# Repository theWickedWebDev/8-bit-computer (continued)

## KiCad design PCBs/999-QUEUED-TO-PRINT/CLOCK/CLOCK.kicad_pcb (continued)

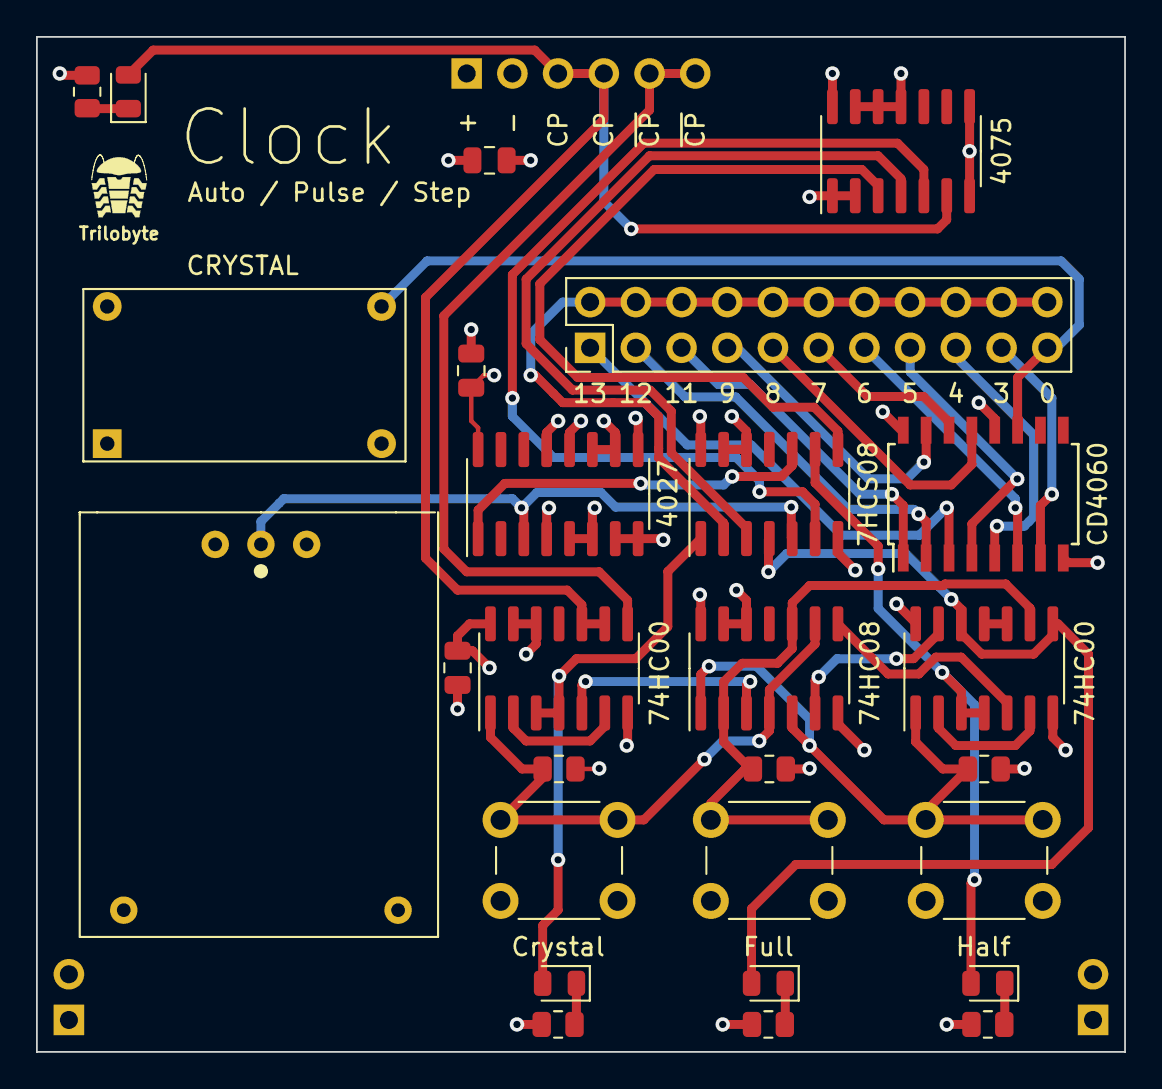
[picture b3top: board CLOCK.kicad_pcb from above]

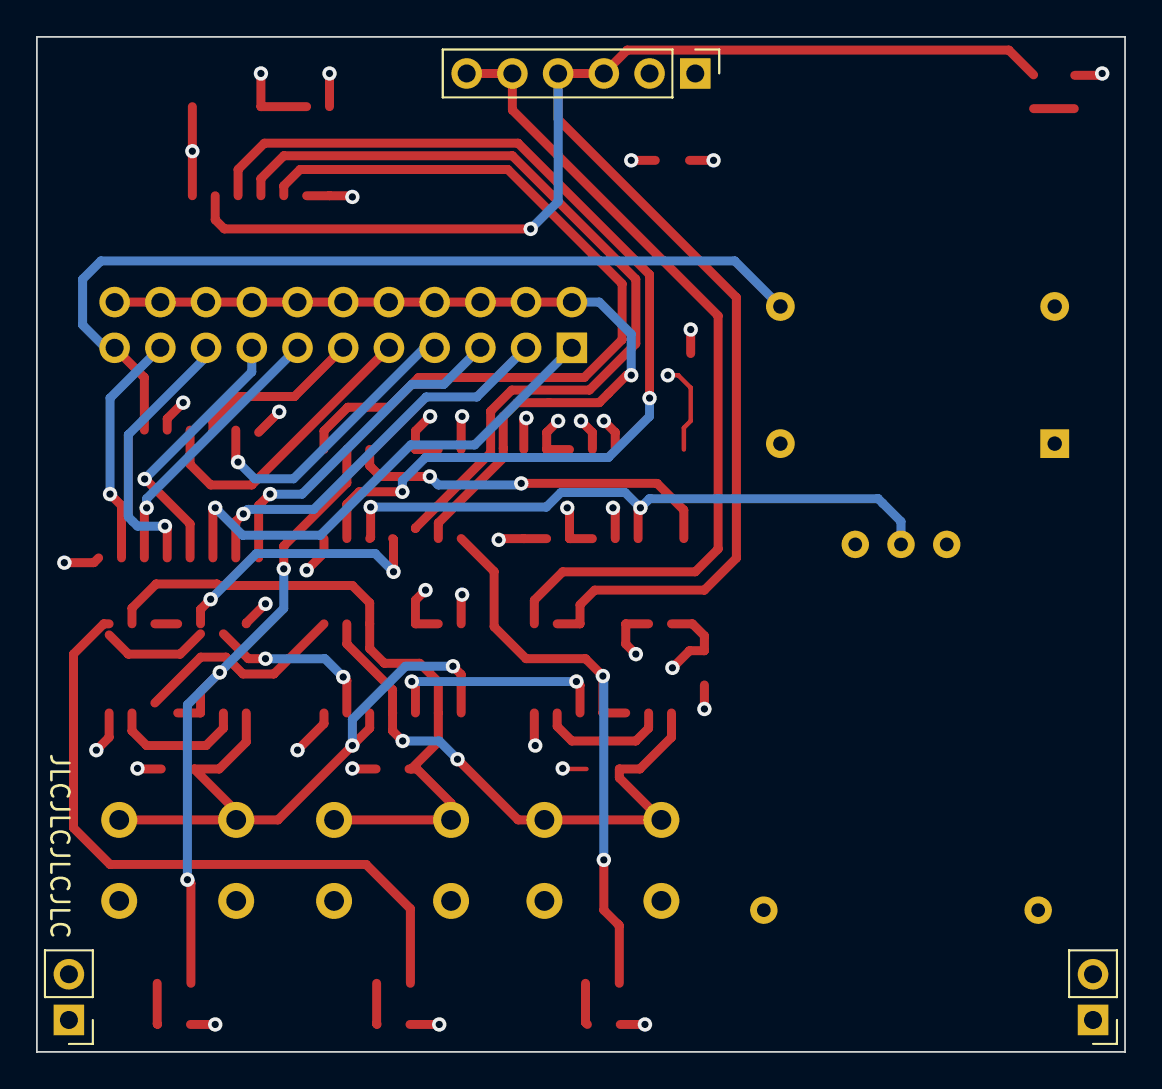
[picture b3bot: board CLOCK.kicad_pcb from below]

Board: 4 copper layers, 60.5 x 56.4 mm, 30 parts (3 on the bottom side), 37 nets.

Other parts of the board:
U4#2: DebouncedButton; COMP-DebounceButton-Component

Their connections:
/MANUAL_FULL_CLOCK: U4#2.3 (Q); also elsewhere on the board
GND: U4#2.2 (Gnd); also elsewhere on the board
VCC: U4#2.1 (Vcc); also elsewhere on the board

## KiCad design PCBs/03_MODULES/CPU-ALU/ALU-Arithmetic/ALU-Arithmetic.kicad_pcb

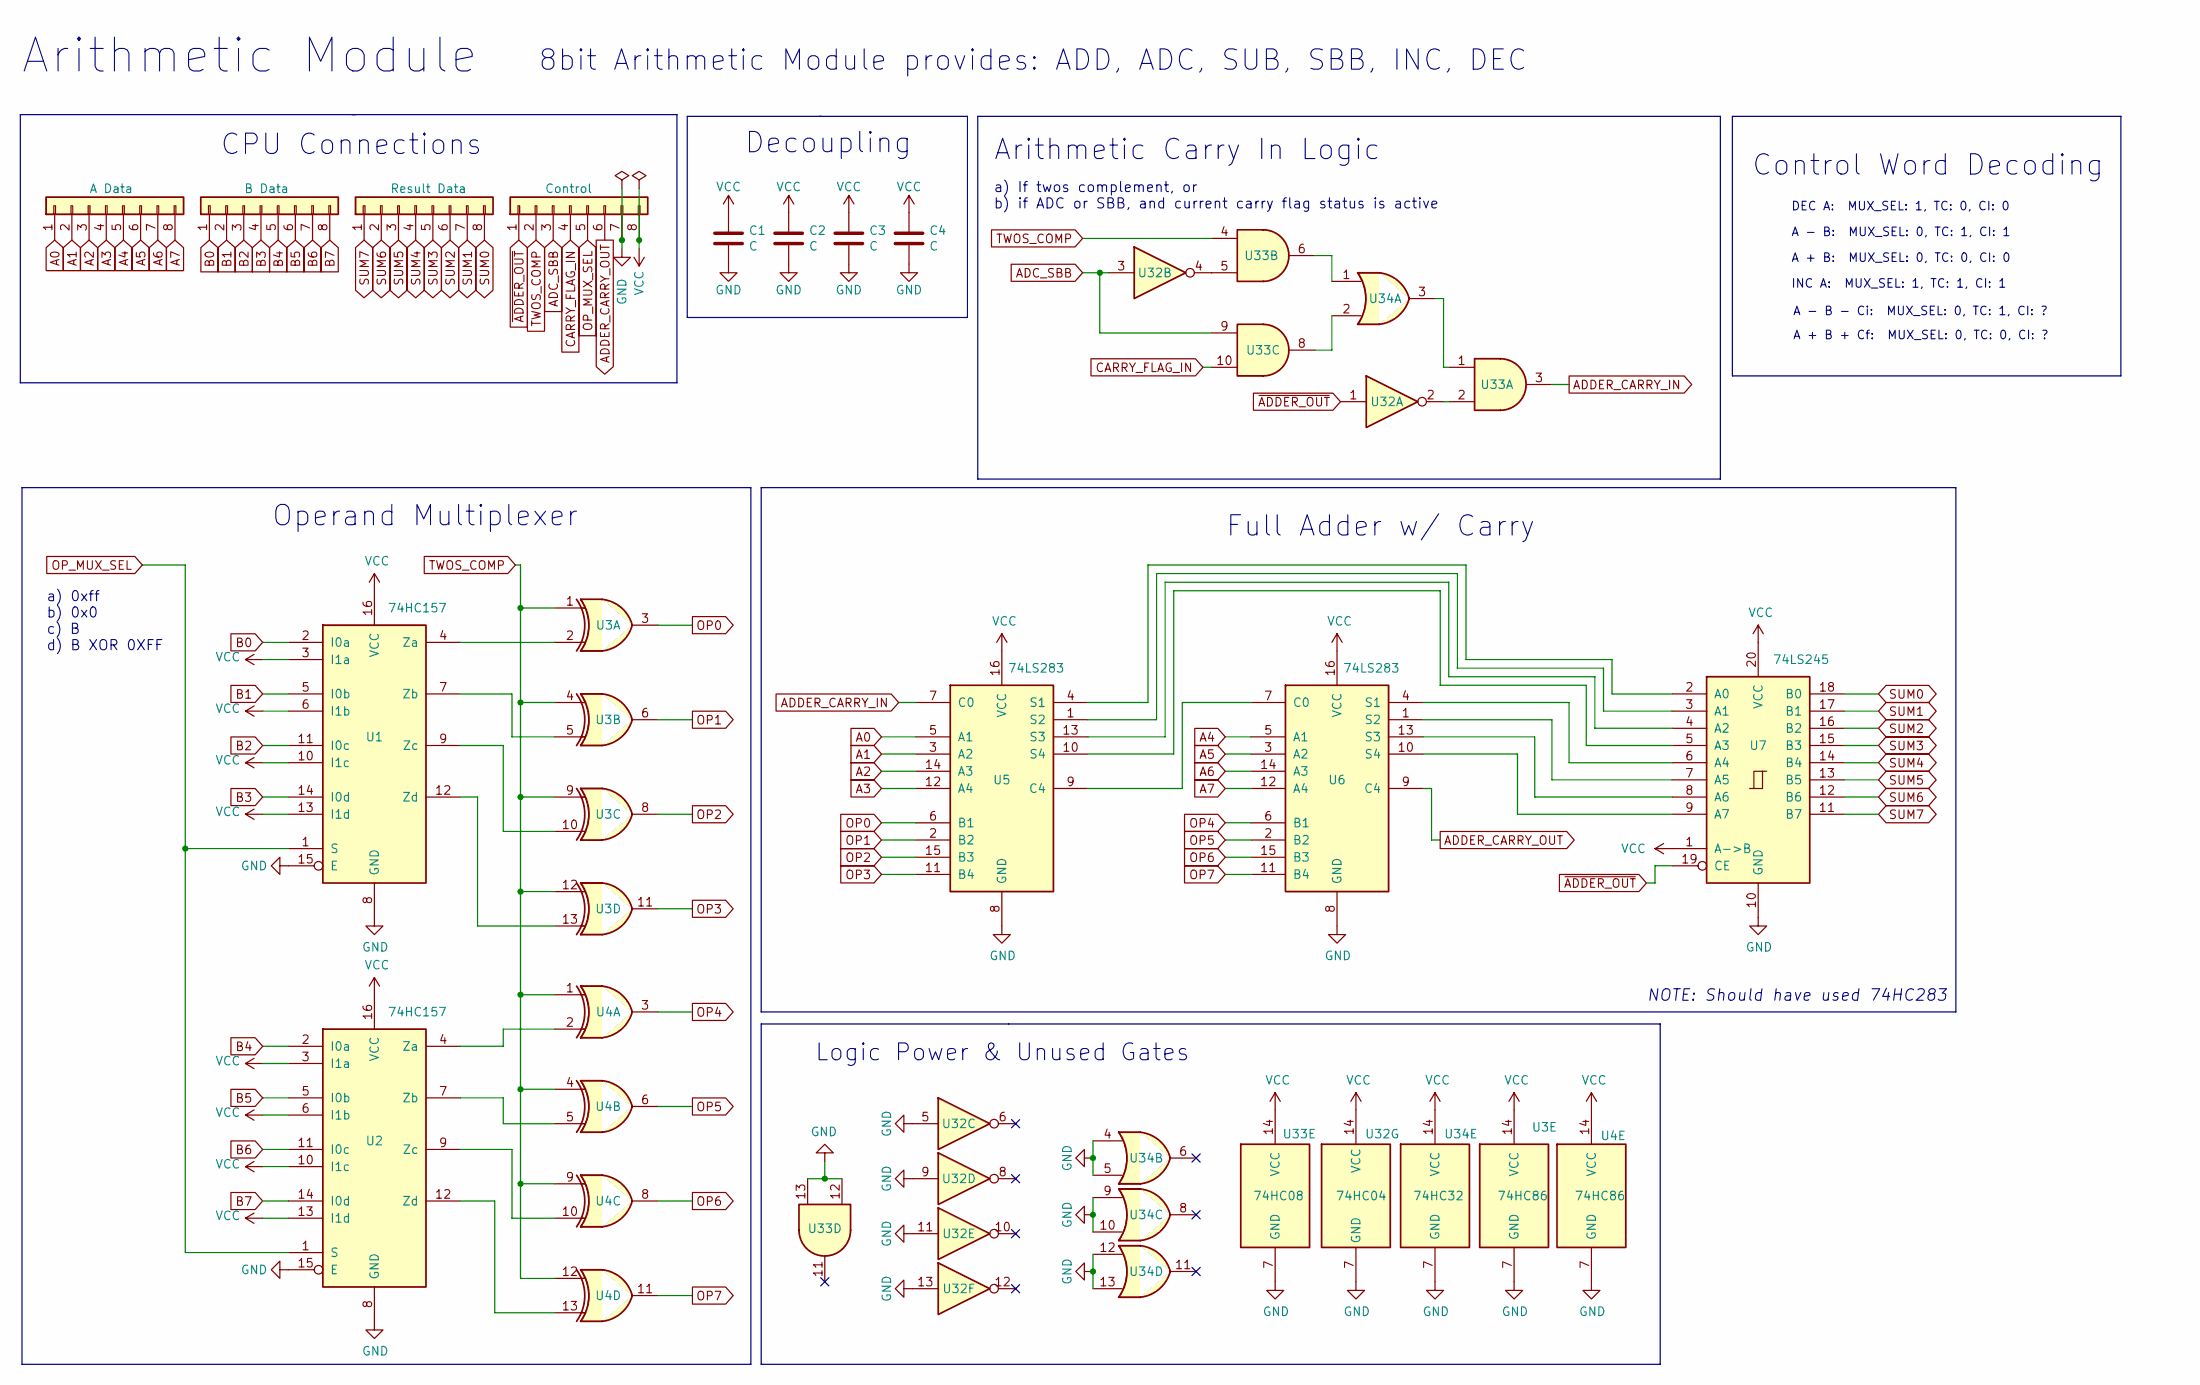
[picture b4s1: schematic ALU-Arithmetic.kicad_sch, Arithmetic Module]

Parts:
C1, C2, C3, C4: C; C_0805_2012Metric
J1, J2, J3, J4: Conn_01x08; PinHeader_1x08_P2.54mm_Vertical
U1, U2: 74HC157; TSSOP-16_4.4x5mm_P0.65mm
U3, U4: 74HC86; TSSOP-14_4.4x5mm_P0.65mm
U5, U6: 74LS283; SOIC-16W_5.3x10.2mm_P1.27mm
U7: 74LS245; TSSOP-20_4.4x6.5mm_P0.65mm
U32: 74HC04; TSSOP-14_4.4x5mm_P0.65mm
U33: 74HC08; TSSOP-14_4.4x5mm_P0.65mm
U34: 74HC32; TSSOP-14_4.4x5mm_P0.65mm

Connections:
A0: J1.1, U5.5 (A1)
A1: J1.2, U5.3 (A2)
A2: J1.3, U5.14 (A3)
A3: J1.4, U5.12 (A4)
A4: J1.5, U6.5 (A1)
A5: J1.6, U6.3 (A2)
A6: J1.7, U6.14 (A3)
A7: J1.8, U6.12 (A4)
ADC_SBB: J4.3, U32.3, U33.9
ADDER_CARRY_IN: U5.7 (C0), U33.3
ADDER_CARRY_OUT: J4.6, U6.9 (C4)
B0: J2.1, U1.2 (I0a)
B1: J2.2, U1.5 (I0b)
B2: J2.3, U1.11 (I0c)
B3: J2.4, U1.14 (I0d)
B4: J2.5, U2.2 (I0a)
B5: J2.6, U2.5 (I0b)
B6: J2.7, U2.11 (I0c)
B7: J2.8, U2.14 (I0d)
CARRY_FLAG_IN: J4.4, U33.10
unnamed: U1.4 (Za), U3.2
unnamed: U1.7 (Zb), U3.5
unnamed: U1.9 (Zc), U3.10
unnamed: U1.12 (Zd), U3.13
unnamed: U2.4 (Za), U4.2
unnamed: U2.7 (Zb), U4.5
unnamed: U2.9 (Zc), U4.10
unnamed: U2.12 (Zd), U4.13
unnamed: U5.1 (S2), U7.3 (A1)
unnamed: U5.4 (S1), U7.2 (A0)
unnamed: U5.9 (C4), U6.7 (C0)
unnamed: U5.10 (S4), U7.5 (A3)
unnamed: U5.13 (S3), U7.4 (A2)
unnamed: U6.1 (S2), U7.7 (A5)
unnamed: U6.4 (S1), U7.6 (A4)
unnamed: U6.10 (S4), U7.9 (A7)
unnamed: U6.13 (S3), U7.8 (A6)
unnamed: U32.2, U33.2
unnamed: U32.4, U33.5
unnamed: U33.1, U34.3
unnamed: U33.6, U34.1
unnamed: U33.8, U34.2
OP0: U3.3, U5.6 (B1)
OP1: U3.6, U5.2 (B2)
OP2: U3.8, U5.15 (B3)
OP3: U3.11, U5.11 (B4)
OP4: U4.3, U6.6 (B1)
OP5: U4.6, U6.2 (B2)
OP6: U4.8, U6.15 (B3)
OP7: U4.11, U6.11 (B4)
OP_MUX_SEL: J4.5, U1.1 (S), U2.1 (S)
SUM0: J3.8, U7.18 (B0)
SUM1: J3.7, U7.17 (B1)
SUM2: J3.6, U7.16 (B2)
SUM3: J3.5, U7.15 (B3)
SUM4: J3.4, U7.14 (B4)
SUM5: J3.3, U7.13 (B5)
SUM6: J3.2, U7.12 (B6)
SUM7: J3.1, U7.11 (B7)
TWOS_COMP: J4.2, U3.1, U3.4, U3.9, U3.12, U4.1, U4.4, U4.9, U4.12, U33.4
VCC: C1.1, C2.1, C3.1, C4.1, J4.8, U1.3 (I1a), U1.6 (I1b), U1.10 (I1c), U1.13 (I1d), U1.16 (VCC), U2.3 (I1a), U2.6 (I1b), U2.10 (I1c), U2.13 (I1d), U2.16 (VCC), U3.14 (VCC), U4.14 (VCC), U5.16 (VCC), U6.16 (VCC), U7.1 (A->B), U7.20 (VCC), U32.14 (VCC), U33.14 (VCC), U34.14 (VCC)
~ADDER_OUT: J4.1, U7.19 (CE), U32.1

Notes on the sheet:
a) 0xff b) 0x0 c) B d) B XOR 0XFF
CPU Connections
NOTE: Should have used 74HC283
8bit Arithmetic Module provides: ADD, ADC, SUB, SBB, INC, DEC
A - B - Ci: MUX_SEL: 0, TC: 1, CI: ?
Logic Power & Unused Gates
A + B + Cf: MUX_SEL: 0, TC: 0, CI: ?
Full Adder w/ Carry
Operand Multiplexer
Arithmetic Module
DEC A: MUX_SEL: 1, TC: 0, CI: 0
a) If twos complement, or b) if ADC or SBB, and current carry flag status is active
Arithmetic Carry In Logic
Decoupling
A - B: MUX_SEL: 0, TC: 1, CI: 1
Control Word Decoding
INC A: MUX_SEL: 1, TC: 1, CI: 1
A + B: MUX_SEL: 0, TC: 0, CI: 0

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
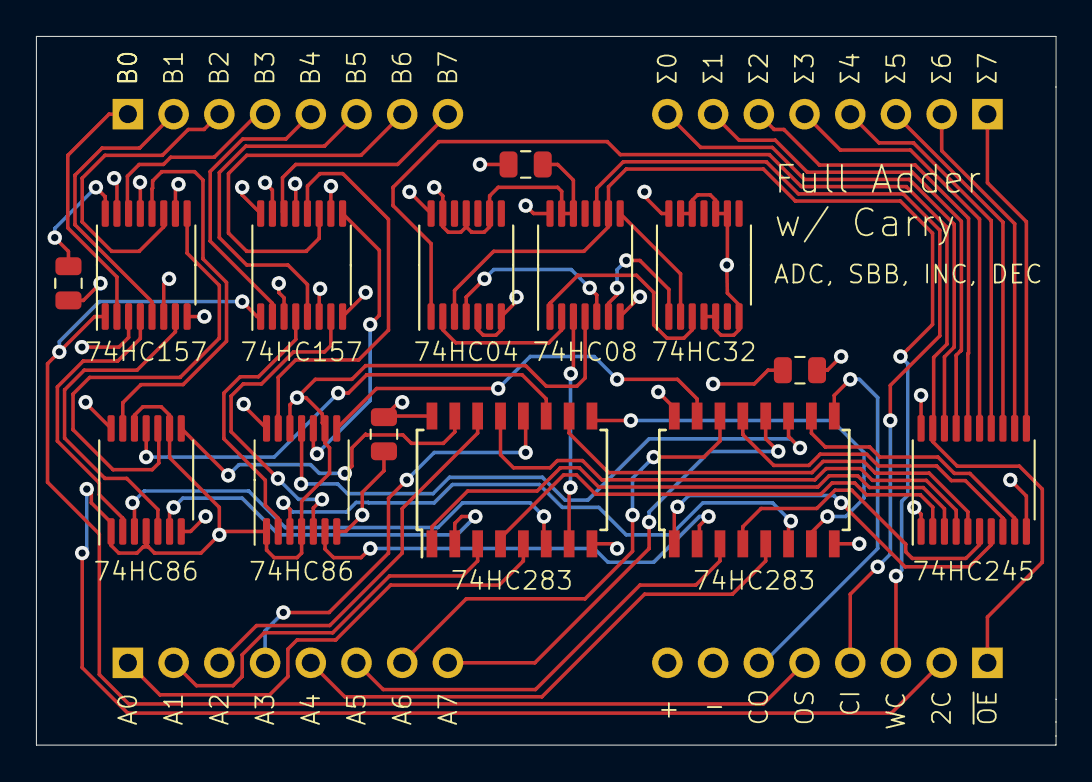
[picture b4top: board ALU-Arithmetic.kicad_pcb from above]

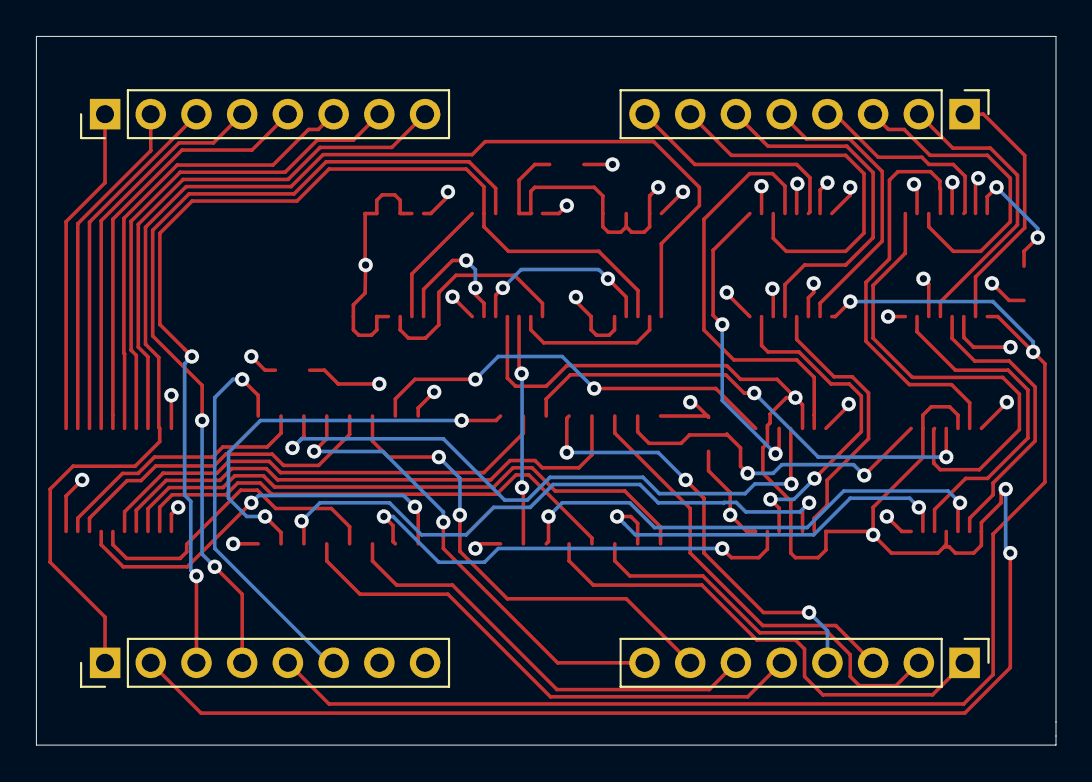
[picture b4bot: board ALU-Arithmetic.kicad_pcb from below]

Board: 4 copper layers, 56.6 x 39.4 mm, 18 parts (4 on the bottom side), 63 nets.

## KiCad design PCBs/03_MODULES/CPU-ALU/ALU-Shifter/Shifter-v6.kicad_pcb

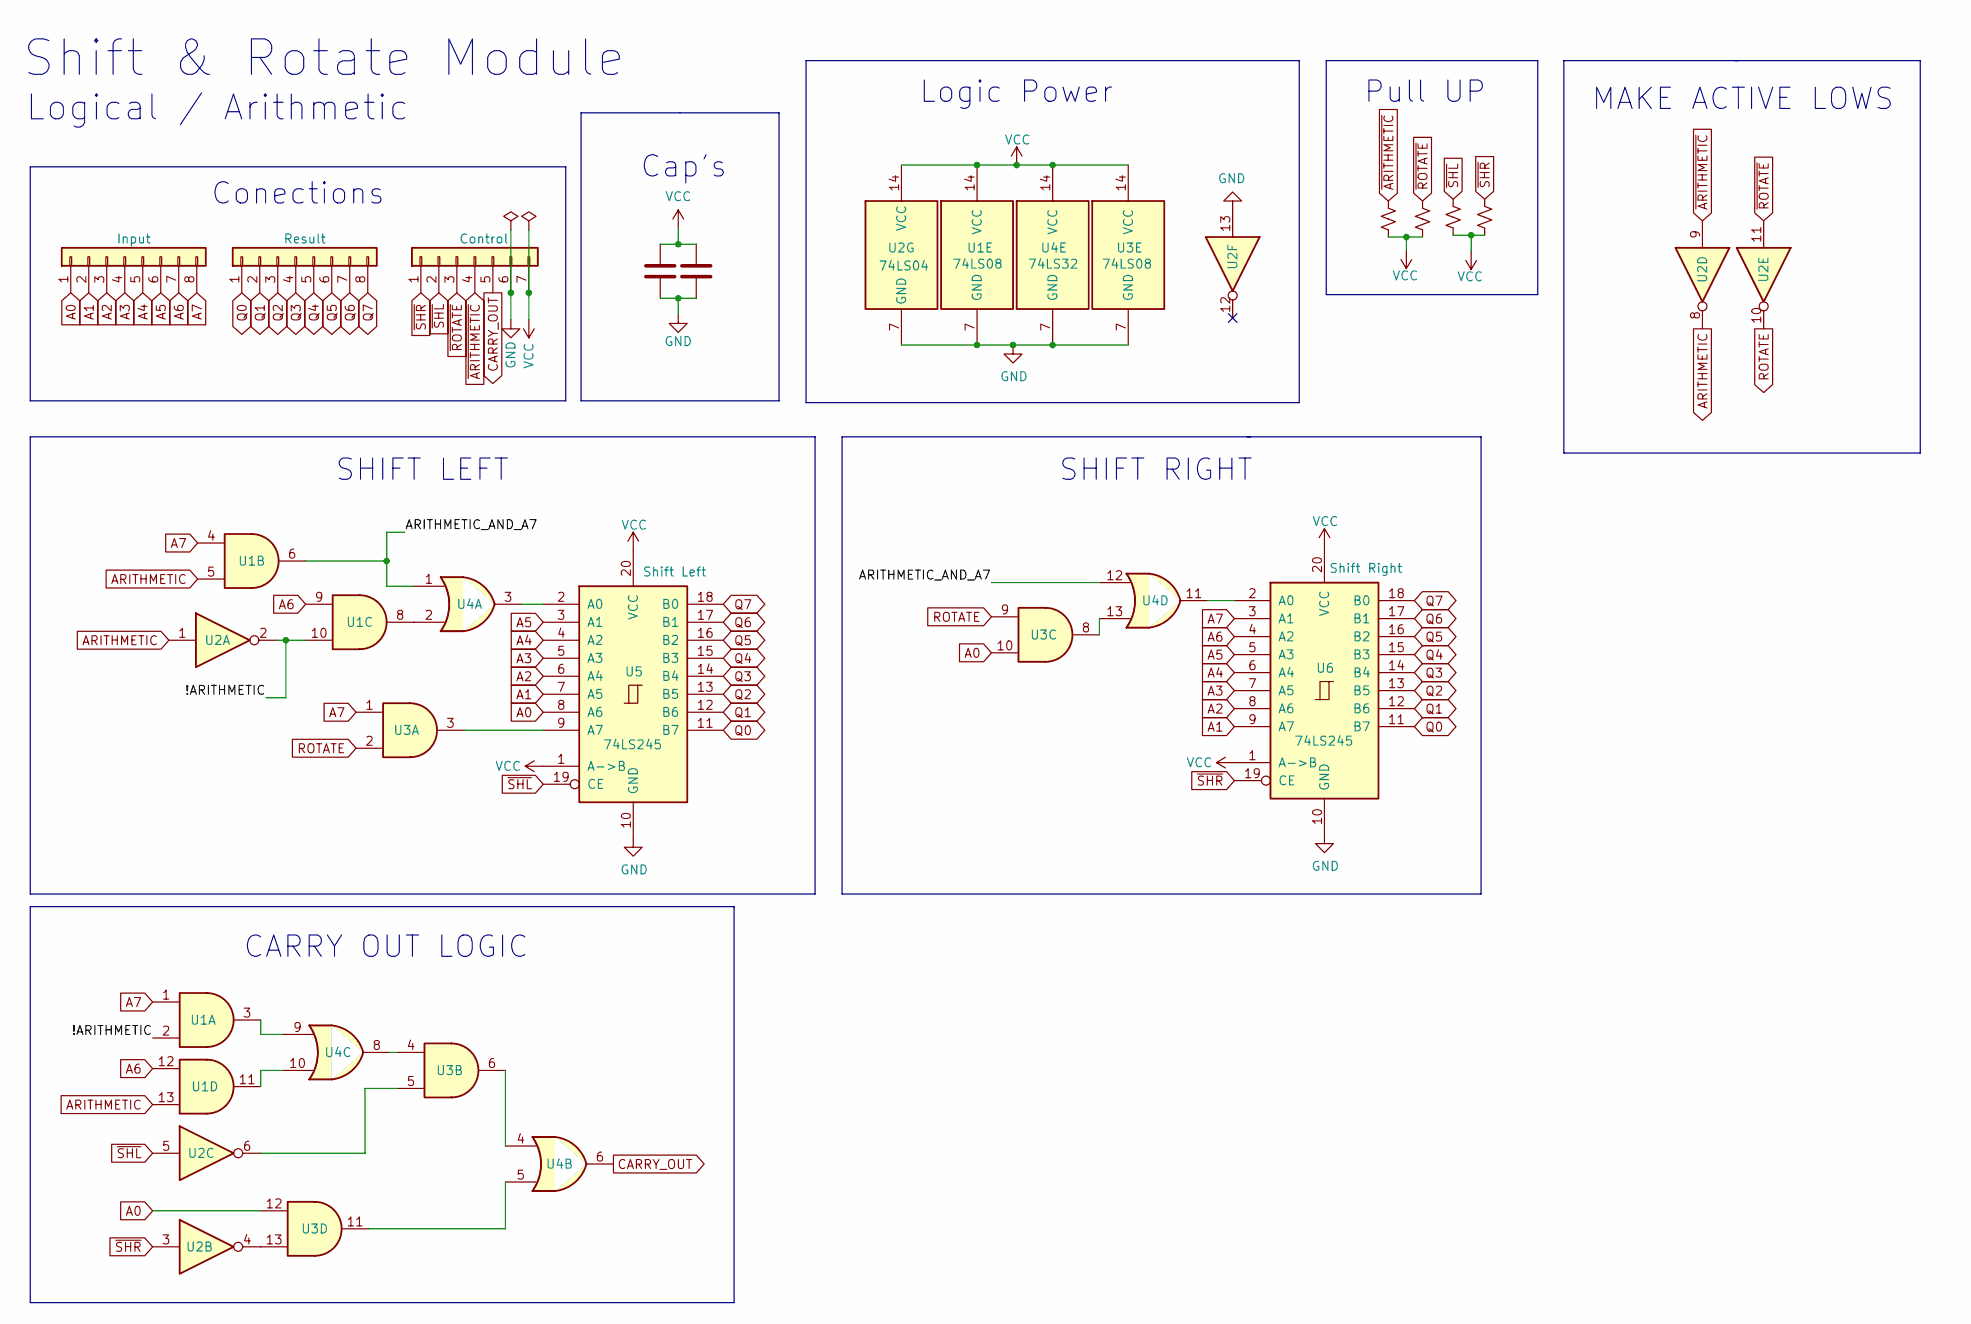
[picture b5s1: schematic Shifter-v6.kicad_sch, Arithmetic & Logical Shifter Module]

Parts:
C1, C2: C; C_0805_2012Metric
J1, J2: Conn_01x08; PinHeader_1x08_P2.54mm_Vertical
J3: Conn_01x07; PinHeader_1x07_P2.54mm_Vertical
R10, R11, R12, R13: R_Small_US; R_0805_2012Metric
U1, U3: 74LS08; TSSOP-14_4.4x5mm_P0.65mm
U2: 74LS04; TSSOP-14_4.4x5mm_P0.65mm
U4: 74LS32; TSSOP-14_4.4x5mm_P0.65mm
U5, U6: 74LS245; TSSOP-20_4.4x6.5mm_P0.65mm

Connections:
/!ARITHMETIC: U1.2, U1.10, U2.2
/ARITHMETIC_AND_A7: U1.6, U4.1, U4.12
A0: J1.1, U3.10, U3.12, U5.8 (A6)
A1: J1.2, U5.7 (A5), U6.9 (A7)
A2: J1.3, U5.6 (A4), U6.8 (A6)
A3: J1.4, U5.5 (A3), U6.7 (A5)
A4: J1.5, U5.4 (A2), U6.6 (A4)
A5: J1.6, U5.3 (A1), U6.5 (A3)
A6: J1.7, U1.9, U1.12, U6.4 (A2)
A7: J1.8, U1.1, U1.4, U3.1, U6.3 (A1)
ARITHMETIC: U1.5, U1.13, U2.1, U2.8
CARRY_OUT: J3.5, U4.6
GND: C1.1, C2.1, J3.6, U1.7 (GND), U2.7 (GND), U2.13, U3.7 (GND), U4.7 (GND), U5.10 (GND), U6.10 (GND)
unnamed: U1.3, U4.9
unnamed: U1.8, U4.2
unnamed: U1.11, U4.10
unnamed: U2.4, U3.13
unnamed: U2.6, U3.5
unnamed: U3.3, U5.9 (A7)
unnamed: U3.4, U4.8
unnamed: U3.6, U4.4
unnamed: U3.8, U4.13
unnamed: U3.11, U4.5
unnamed: U4.3, U5.2 (A0)
unnamed: U4.11, U6.2 (A0)
Q0: J2.1, U5.11 (B7), U6.11 (B7)
Q1: J2.2, U5.12 (B6), U6.12 (B6)
Q2: J2.3, U5.13 (B5), U6.13 (B5)
Q3: J2.4, U5.14 (B4), U6.14 (B4)
Q4: J2.5, U5.15 (B3), U6.15 (B3)
Q5: J2.6, U5.16 (B2), U6.16 (B2)
Q6: J2.7, U5.17 (B1), U6.17 (B1)
Q7: J2.8, U5.18 (B0), U6.18 (B0)
ROTATE: U2.10, U3.2, U3.9
~ARITHMETIC: J3.4, R13.1, U2.9
~ROTATE: J3.3, R10.1, U2.11
~SHL: J3.2, R11.1, U2.5, U5.19 (CE)
~SHR: J3.1, R12.1, U2.3, U6.19 (CE)

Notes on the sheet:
Cap's
Shift & Rotate Module
SHIFT RIGHT
SHIFT LEFT
Conections
Logic Power
MAKE ACTIVE LOWS
Pull UP
Logical / Arithmetic
CARRY OUT LOGIC

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
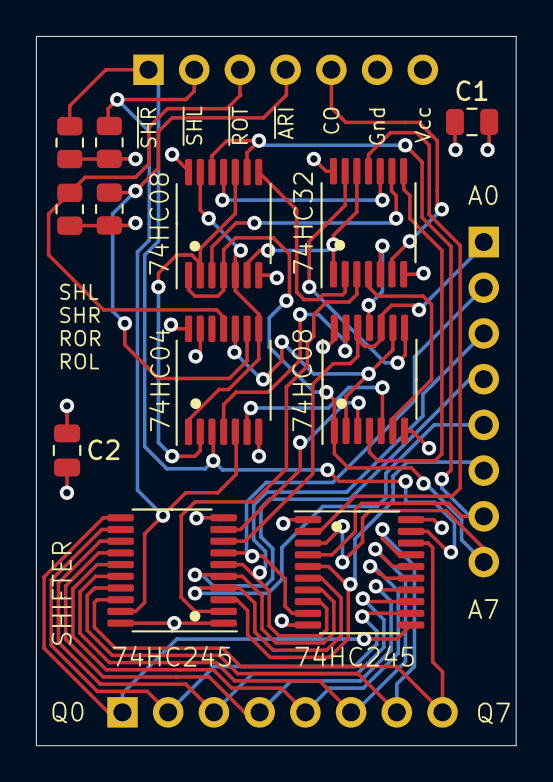
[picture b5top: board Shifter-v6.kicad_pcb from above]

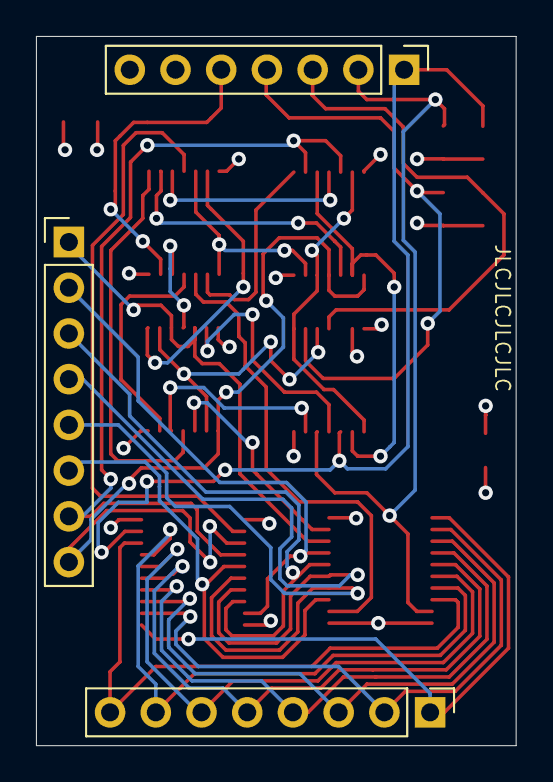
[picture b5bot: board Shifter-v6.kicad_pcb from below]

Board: 4 copper layers, 26.7 x 39.4 mm, 15 parts (3 on the bottom side), 39 nets.

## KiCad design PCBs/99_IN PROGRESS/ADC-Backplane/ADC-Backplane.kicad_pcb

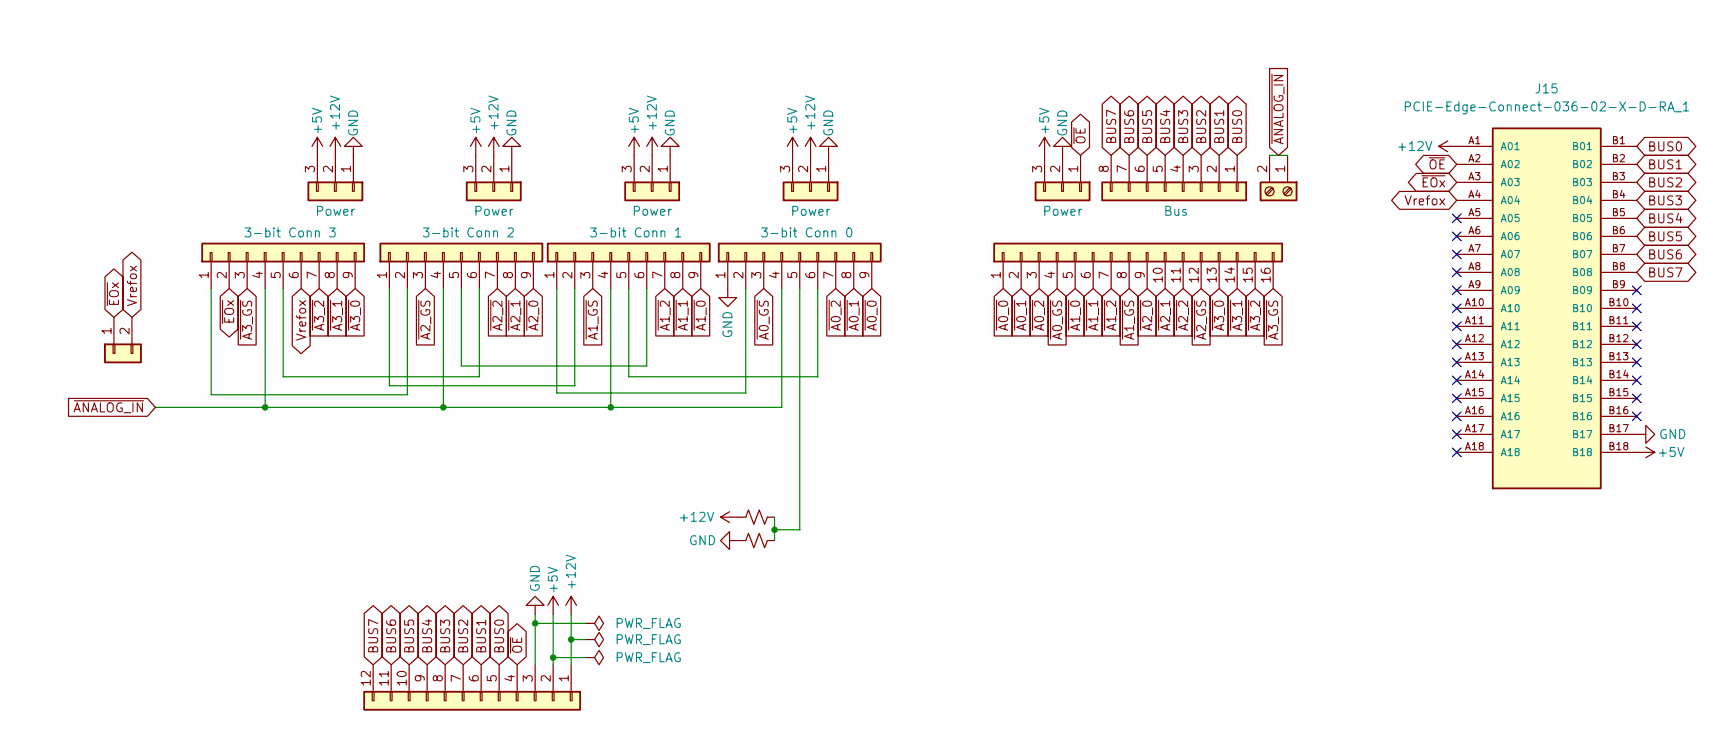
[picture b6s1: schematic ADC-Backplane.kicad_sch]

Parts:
J1: Conn_01x02; PinHeader_1x02_P2.54mm_Horizontal
J2, J4, J7, J9: Conn_01x09; PinSocket_1x09_P2.54mm_Vertical
J3, J6, J8, J10, J11: Conn_01x03; PinSocket_1x03_P2.54mm_Vertical
J5: Conn_01x12; PinHeader_1x12_P2.54mm_Horizontal
J12: Conn_01x16; PinSocket_1x16_P2.54mm_Vertical
J13: Conn_01x08; PinSocket_1x08_P2.54mm_Vertical
J14: Screw_Terminal_01x02; TerminalBlock_TE_282834-2_1x02_P2.54mm_Horizontal
J15: PCIE-Edge-Connect-036-02-X-D-RA_1; BUS_PCIexpress_x1; PARTREV D
R1, R2: R_Small_US; R_0805_2012Metric

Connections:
+5V: J3.3, J5.2, J6.3, J8.3, J10.3, J11.3, J15.B18
+12V: J3.2, J5.1, J6.2, J8.2, J10.2, J15.A1 (A01), R1.2
BUS0: J5.5, J13.1, J15.B1 (B01)
BUS1: J5.6, J13.2, J15.B2 (B02)
BUS2: J5.7, J13.3, J15.B3 (B03)
BUS3: J5.8, J13.4, J15.B4 (B04)
BUS4: J5.9, J13.5, J15.B5 (B05)
BUS5: J5.10, J13.6, J15.B6 (B06)
BUS6: J5.11, J13.7, J15.B7 (B07)
BUS7: J5.12, J13.8, J15.B8 (B08)
GND: J3.1, J5.3, J6.1, J8.1, J9.1, J10.1, J11.2, J15.B17, R2.2
unnamed: J2.1, J4.2
unnamed: J2.5, J4.6
unnamed: J4.1, J7.2
unnamed: J4.5, J7.6
unnamed: J7.1, J9.2
unnamed: J7.5, J9.6
unnamed: J9.5, R1.1, R2.1
Vrefox: J1.2, J2.6, J15.A4 (A04)
~A0_0: J9.9, J12.1
~A0_1: J9.8, J12.2
~A0_2: J9.7, J12.3
~A0_GS: J9.3, J12.4
~A1_0: J7.9, J12.5
~A1_1: J7.8, J12.6
~A1_2: J7.7, J12.7
~A1_GS: J7.3, J12.8
~A2_0: J4.9, J12.9
~A2_1: J4.8, J12.10
~A2_2: J4.7, J12.11
~A2_GS: J4.3, J12.12
~A3_0: J2.9, J12.13
~A3_1: J2.8, J12.14
~A3_2: J2.7, J12.15
~A3_GS: J2.3, J12.16
~ANALOG_IN: J2.4, J4.4, J7.4, J9.4, J14.1, J14.2
~EOx: J1.1, J2.2, J15.A3 (A03)
~OE: J5.4, J11.1, J15.A2 (A02)

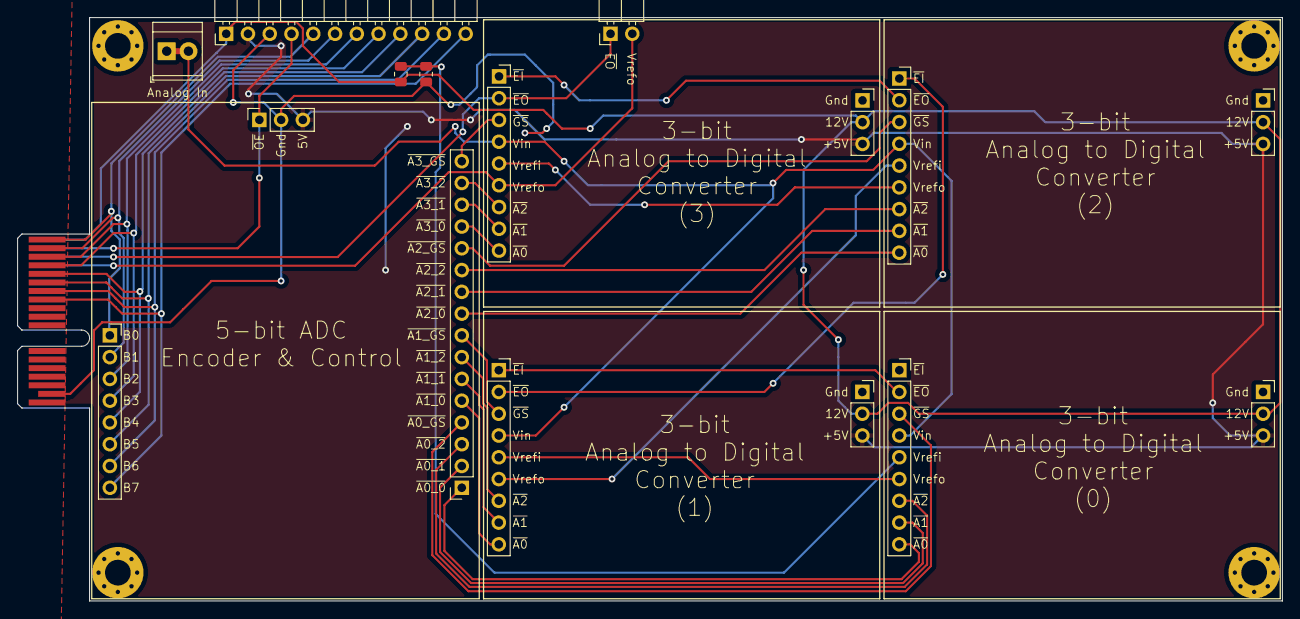
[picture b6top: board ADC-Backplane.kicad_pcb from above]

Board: 2 copper layers, 147.6 x 68.1 mm, 17 parts (0 on the bottom side), 38 nets.

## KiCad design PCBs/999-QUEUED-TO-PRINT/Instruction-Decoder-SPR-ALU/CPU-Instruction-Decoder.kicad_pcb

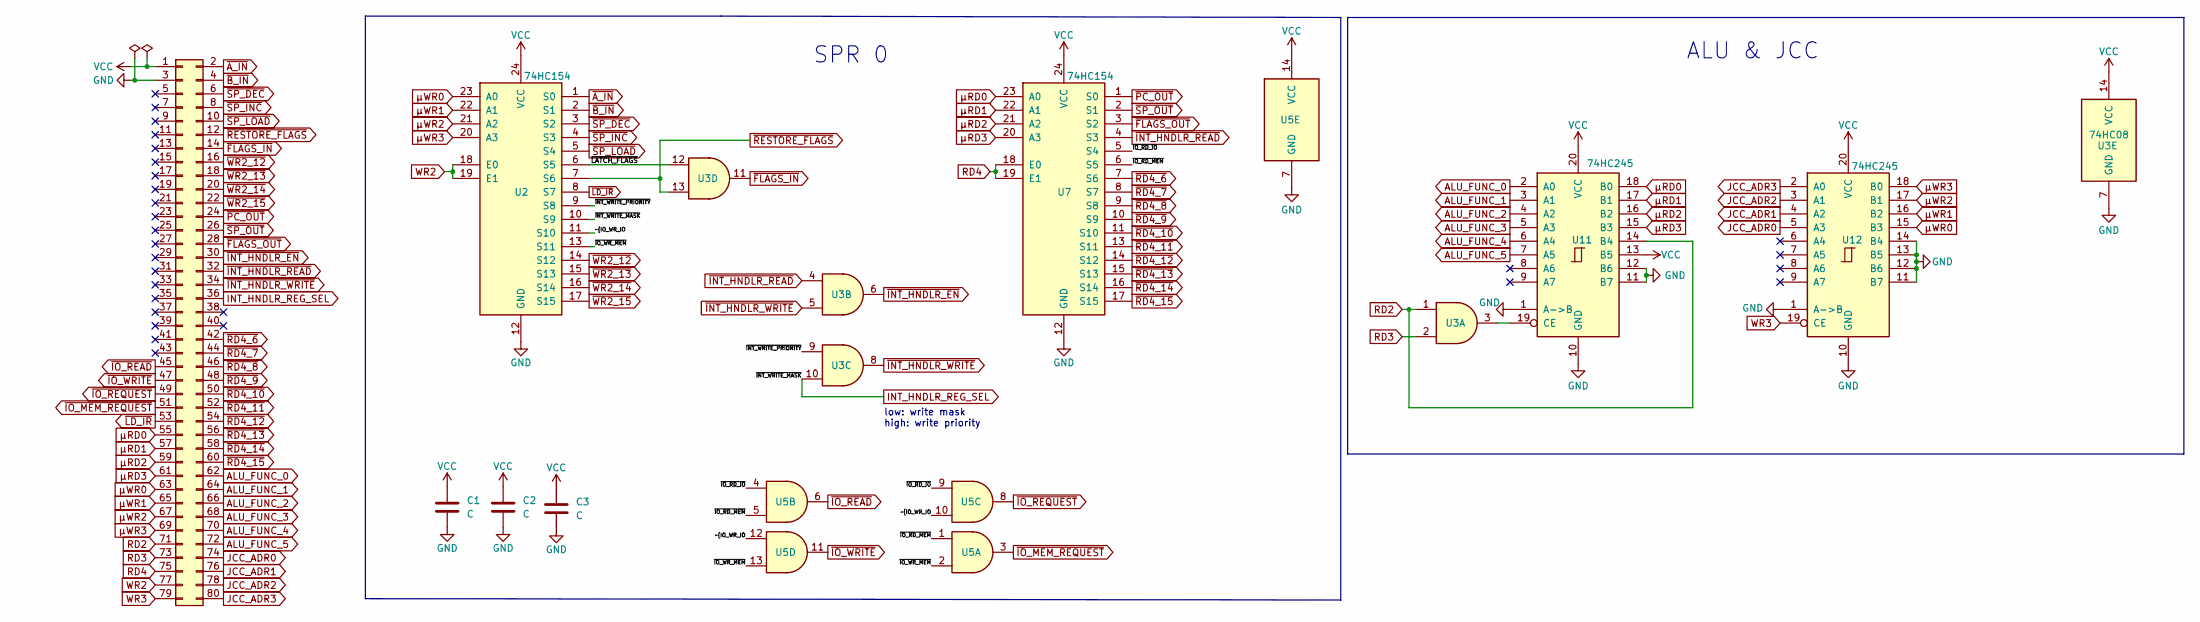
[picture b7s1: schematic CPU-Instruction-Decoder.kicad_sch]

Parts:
C1, C2, C3: C; C_0805_2012Metric
J1: Conn_02x40_Odd_Even; PinHeader_2x40_P2.54mm_Horizontal
U2, U7: 74HC154; SOIC-24W_7.5x15.4mm_P1.27mm
U3, U5: 74HC08; SOIC-14_3.9x8.7mm_P1.27mm
U11, U12: 74HC245; SOIC-20W_7.5x12.8mm_P1.27mm

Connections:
/~INT_WRITE_PRIORITY: U2.9 (S8), U3.9
/~IO_RD_IO: U5.4, U5.9, U7.5 (S4)
/~IO_RD_MEM: U5.1, U5.5, U7.6 (S5)
/~IO_WR_IO: U2.11 (S10), U5.10, U5.12
/~IO_WR_MEM: U2.13 (S11), U5.2, U5.13
/~LATCH_FLAGS: U2.6 (S5), U3.12
ALU_FUNC_0: J1.62, U11.2 (A0)
ALU_FUNC_1: J1.64, U11.3 (A1)
ALU_FUNC_2: J1.66, U11.4 (A2)
ALU_FUNC_3: J1.68, U11.5 (A3)
ALU_FUNC_4: J1.70, U11.6 (A4)
ALU_FUNC_5: J1.72, U11.7 (A5)
GND: C1.2, C2.2, C3.2, J1.3, U2.12 (GND), U3.7 (GND), U5.7 (GND), U7.12 (GND), U11.1 (A->B), U11.10 (GND), U11.11 (B7), U11.12 (B6), U12.1 (A->B), U12.10 (GND), U12.11 (B7), U12.12 (B6), U12.13 (B5), U12.14 (B4)
INT_HNDLR_REG_SEL: J1.36, U2.10 (S9), U3.10
JCC_ADR0: J1.74, U12.5 (A3)
JCC_ADR1: J1.76, U12.4 (A2)
JCC_ADR2: J1.78, U12.3 (A1)
JCC_ADR3: J1.80, U12.2 (A0)
unnamed: U3.3, U11.19 (CE)
RD2: J1.71, U3.1, U11.14 (B4)
RD3: J1.73, U3.2
RD4: J1.75, U7.18 (E0), U7.19 (E1)
VCC: C1.1, C2.1, C3.1, J1.1, U2.24 (VCC), U3.14 (VCC), U5.14 (VCC), U7.24 (VCC), U11.13 (B5), U11.20 (VCC), U12.20 (VCC)
WR2: J1.77, U2.18 (E0), U2.19 (E1)
WR3: J1.79, U12.19 (CE)
~A_IN: J1.2, U2.1 (S0)
~B_IN: J1.4, U2.2 (S1)
~FLAGS_IN: J1.14, U3.11
~FLAGS_OUT: J1.28, U7.3 (S2)
~INT_HNDLR_EN: J1.30, U3.6
~INT_HNDLR_READ: J1.32, U3.4, U7.4 (S3)
~INT_HNDLR_WRITE: J1.34, U3.5, U3.8
~IO_MEM_REQUEST: J1.51, U5.3
~IO_READ: J1.45, U5.6
~IO_REQUEST: J1.49, U5.8
~IO_WRITE: J1.47, U5.11
~LD_IR: J1.53, U2.8 (S7)
~PC_OUT: J1.24, U7.1 (S0)
~RD4_6: J1.42, U7.7 (S6)
~RD4_7: J1.44, U7.8 (S7)
~RD4_8: J1.46, U7.9 (S8)
~RD4_9: J1.48, U7.10 (S9)
~RD4_10: J1.50, U7.11 (S10)
~RD4_11: J1.52, U7.13 (S11)
~RD4_12: J1.54, U7.14 (S12)
~RD4_13: J1.56, U7.15 (S13)
~RD4_14: J1.58, U7.16 (S14)
~RD4_15: J1.60, U7.17 (S15)
~RESTORE_FLAGS: J1.12, U2.7 (S6), U3.13
~SP_DEC: J1.6, U2.3 (S2)
~SP_INC: J1.8, U2.4 (S3)
~SP_LOAD: J1.10, U2.5 (S4)
~SP_OUT: J1.26, U7.2 (S1)
~WR2_12: J1.16, U2.14 (S12)
~WR2_13: J1.18, U2.15 (S13)
~WR2_14: J1.20, U2.16 (S14)
~WR2_15: J1.22, U2.17 (S15)
μRD0: J1.55, U7.23 (A0), U11.18 (B0)
μRD1: J1.57, U7.22 (A1), U11.17 (B1)
μRD2: J1.59, U7.21 (A2), U11.16 (B2)
μRD3: J1.61, U7.20 (A3), U11.15 (B3)
μWR0: J1.63, U2.23 (A0), U12.15 (B3)
μWR1: J1.65, U2.22 (A1), U12.16 (B2)
μWR2: J1.67, U2.21 (A2), U12.17 (B1)
μWR3: J1.69, U2.20 (A3), U12.18 (B0)

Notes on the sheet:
ALU & JCC
low: write mask high: write priority
SPR 0

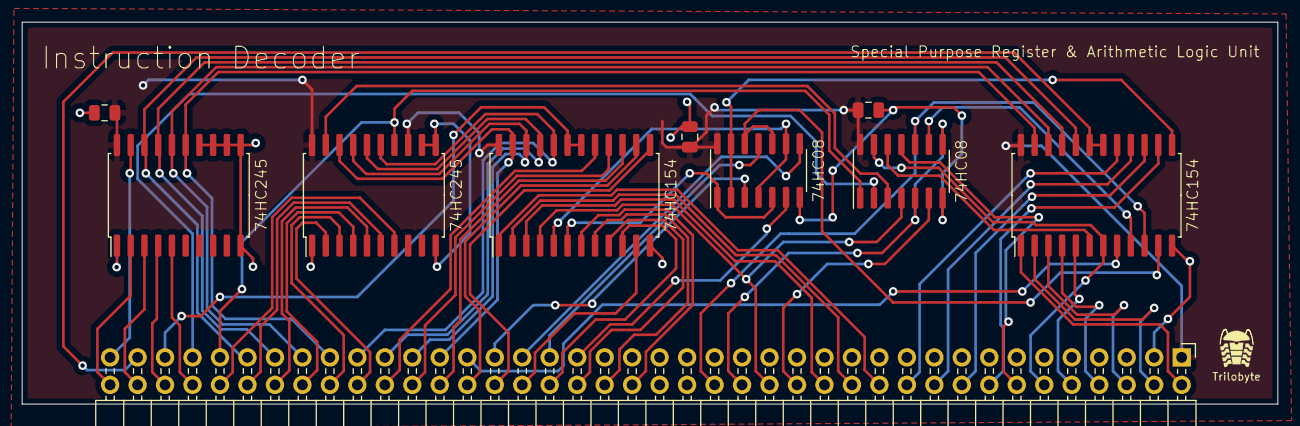
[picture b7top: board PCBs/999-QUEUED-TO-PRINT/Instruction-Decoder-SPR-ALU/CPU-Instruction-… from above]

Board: 2 copper layers, 116.1 x 35.3 mm, 10 parts (0 on the bottom side), 65 nets.
